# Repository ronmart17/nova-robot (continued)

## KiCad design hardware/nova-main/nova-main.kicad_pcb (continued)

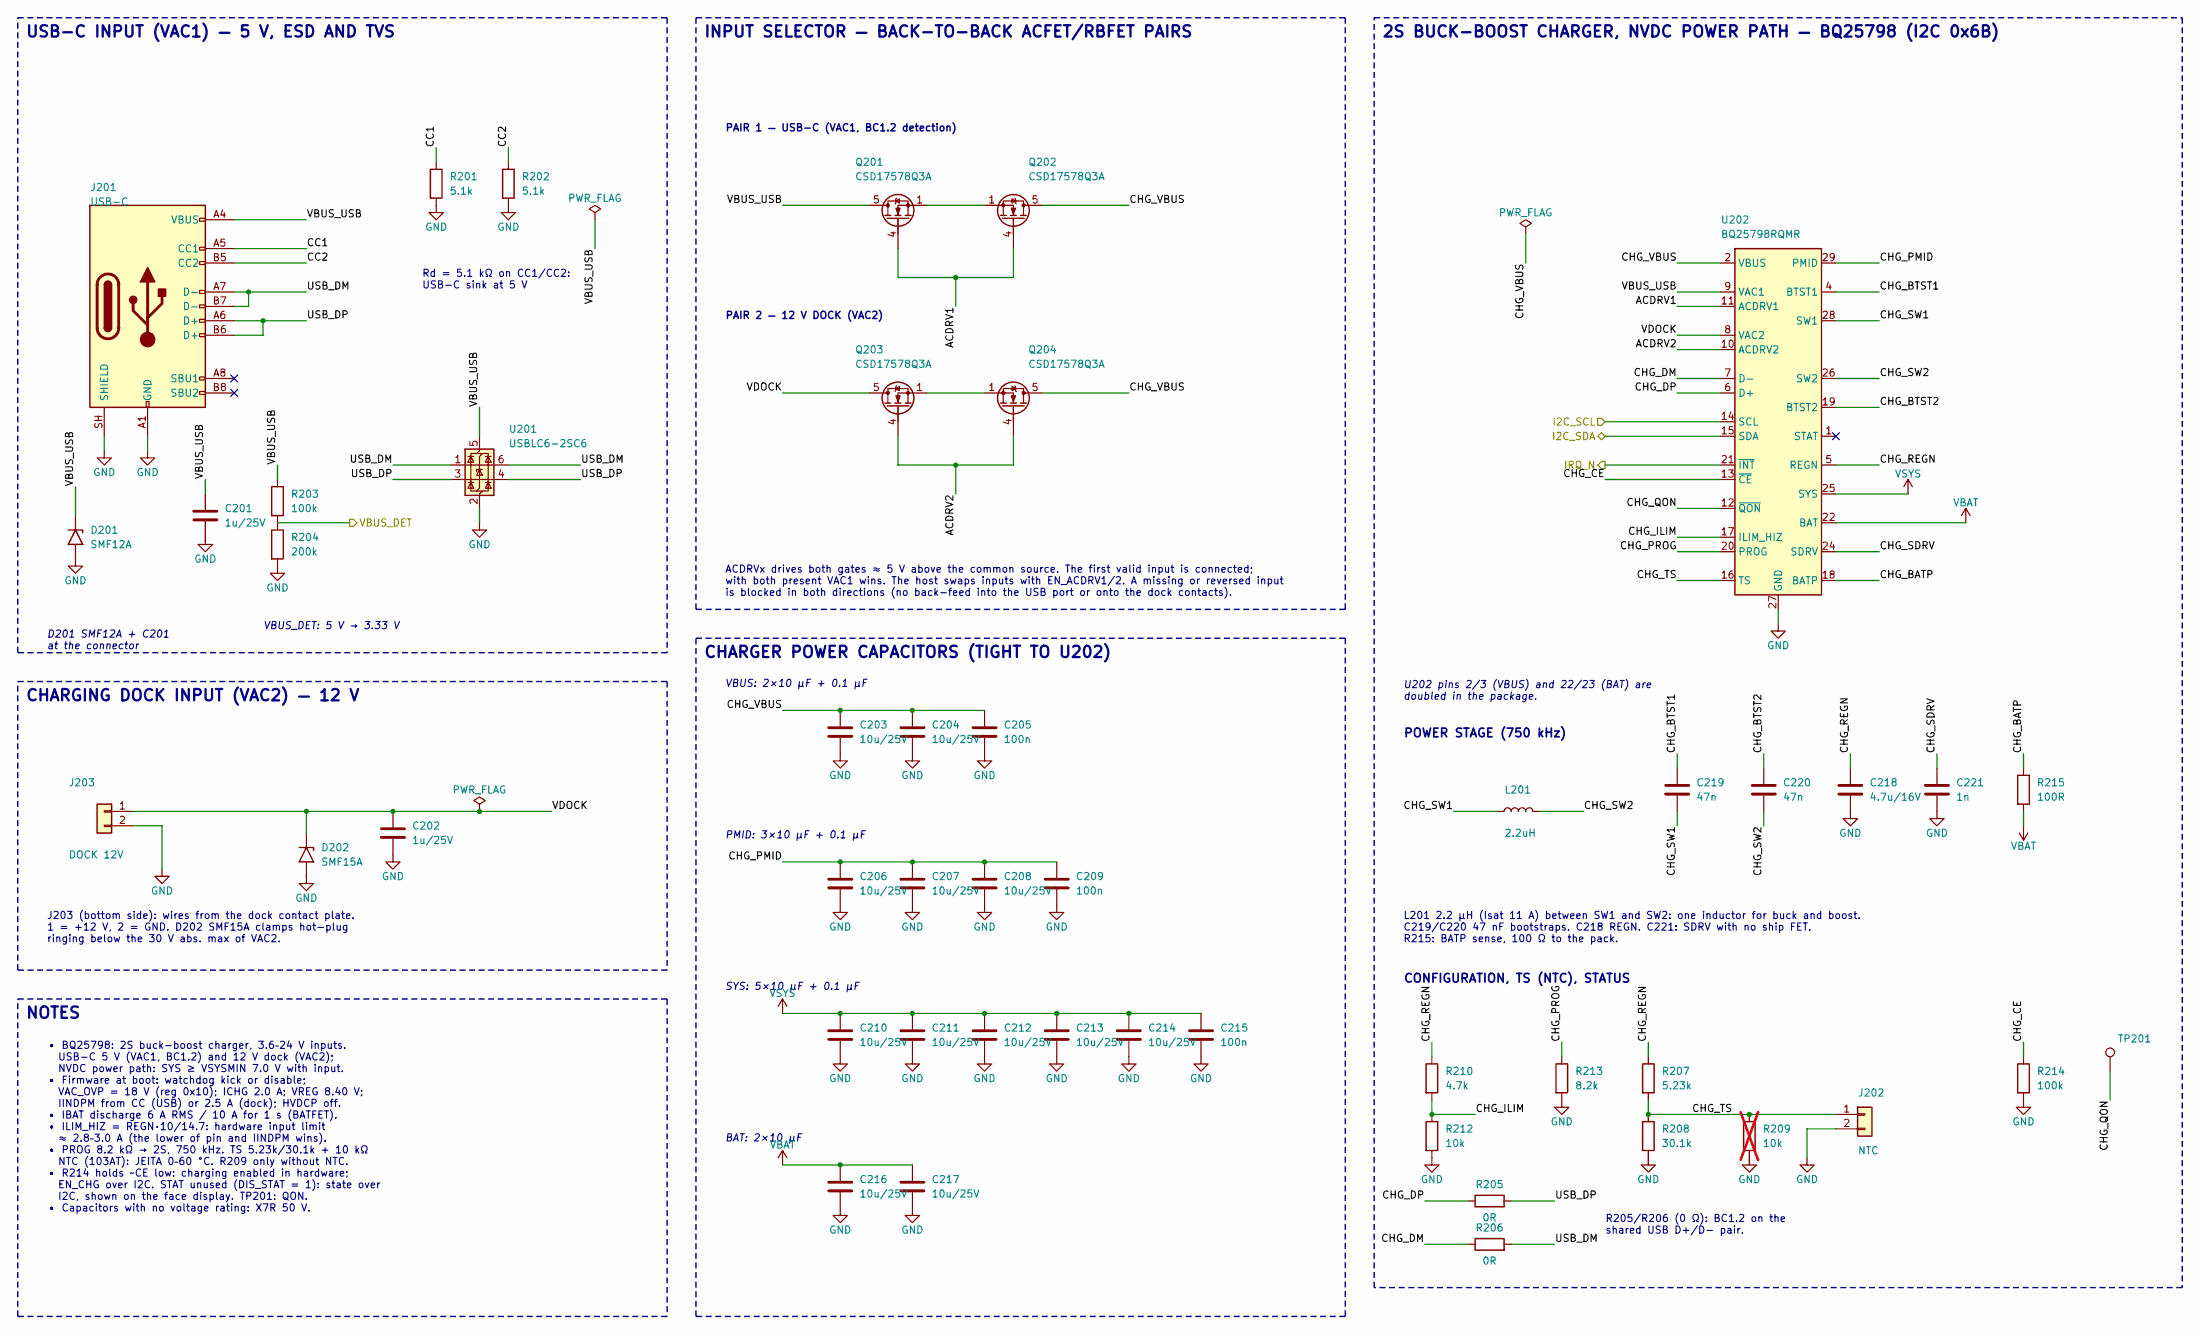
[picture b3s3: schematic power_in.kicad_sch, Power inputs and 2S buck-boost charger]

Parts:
C201, C202: 1u/25V; C_0603_1608Metric; Voltage 25V; MPN CC0603KRX5R8BB105; LCSC C14664
C203, C204, C206, C207, C208, C210, C211, C212, C213, C214, C216, C217: 10u/25V; C_0805_2012Metric; Voltage 25V; MPN CL21A106KAYNNNE; LCSC C15850
C205, C209, C215: 100n; C_0402_1005Metric; Voltage 50V; MPN CL05B104KB54PNC; LCSC C307331
C218: 4.7u/16V; C_0603_1608Metric; Voltage 16V; MPN CL10A475KO8NNNC; LCSC C19666
C219, C220: 47n; C_0402_1005Metric; Voltage 25V; MPN CL05B473KA5NNNC; LCSC C318631
C221: 1n; C_0402_1005Metric; Voltage 50V; MPN CL05B102KB5NNNC; LCSC C14442
D201: SMF12A; D_SMF; MPN SMF12A; LCSC C123800
D202: SMF15A; D_SMF; MPN SMF15A; LCSC C123802
J201: USB-C; USB_C_Receptacle_HRO_TYPE-C-31-M-12_GCT_USB4105; MPN TYPE-C-31-M-12; LCSC C165948
J202: NTC; JST_PH_B2B-PH-K_1x02_P2.00mm_Vertical; MPN B2B-PH-K-S(LF)(SN); LCSC C131337
J203: DOCK 12V; JST_XH_B2B-XH-A_1x02_P2.50mm_Vertical; MPN B2B-XH-A(LF)(SN); LCSC C158012
L201: 2.2uH; L_Sunlord_MWSA0605S; MPN MWSA0605S-2R2MT; LCSC C408463
Q201, Q202, Q203, Q204: CSD17578Q3A; VSON-8_3.3x3.3mm_P0.65mm_NexFET; MPN CSD17578Q3A; LCSC C205986
R201, R202: 5.1k; R_0402_1005Metric; Tolerance 1%; MPN RC0402FR-075K1L; LCSC C105872
R203, R214: 100k; R_0402_1005Metric; Tolerance 1%; MPN RC0402FR-07100KL; LCSC C60491
R204: 200k; R_0402_1005Metric; Tolerance 1%; MPN RC0402FR-07200KL; LCSC C114763
R205, R206: 0R; R_0402_1005Metric; Tolerance 1%; MPN RC0402JR-070RL; LCSC C60485
R207: 5.23k; R_0402_1005Metric; Tolerance 1%; MPN CRCW04025K23FKED; LCSC C2076550
R208: 30.1k; R_0402_1005Metric; Tolerance 1%; MPN ERJ-2RKF3012X; LCSC C2076806
R209: 10k; R_0402_1005Metric; Tolerance 1%; MPN RC0402FR-0710KL; LCSC C60490; not fitted
R210: 4.7k; R_0402_1005Metric; Tolerance 1%; MPN RC0402FR-074K7L; LCSC C105871
R212: 10k; R_0402_1005Metric; Tolerance 1%; MPN RC0402FR-0710KL; LCSC C60490
R213: 8.2k; R_0402_1005Metric; Tolerance 1%; MPN 0402WGF8201TCE; LCSC C25924
R215: 100R; R_0402_1005Metric; Tolerance 1%; MPN RC0402FR-07100RL; LCSC C106232
TP201: TP; TestPoint_Pad_D1.5mm
U201: USBLC6-2SC6; SOT-23-6; MPN USBLC6-2SC6; LCSC C7519
U202: BQ25798RQMR; Texas_RQM0029A_VQFN-29_4x4mm_P0.4mm; MPN BQ25798RQMR; LCSC C2876593

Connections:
/I2C_SCL: U202.14 (SCL); also elsewhere on the board
/I2C_SDA: U202.15 (SDA); also elsewhere on the board
/IRQ_N: U202.21 (~INT); also elsewhere on the board
/USB-C + 12 V dock, BQ25798 charger/ACDRV1: Q201.4 (G), Q202.4 (G), U202.11 (ACDRV1)
/USB-C + 12 V dock, BQ25798 charger/ACDRV2: Q203.4 (G), Q204.4 (G), U202.10 (ACDRV2)
/USB-C + 12 V dock, BQ25798 charger/CC1: J201.A5 (CC1), R201.1
/USB-C + 12 V dock, BQ25798 charger/CC2: J201.B5 (CC2), R202.1
/USB-C + 12 V dock, BQ25798 charger/CHG_BATP: R215.1, U202.18 (BATP)
/USB-C + 12 V dock, BQ25798 charger/CHG_BTST1: C219.1, U202.4 (BTST1)
/USB-C + 12 V dock, BQ25798 charger/CHG_BTST2: C220.1, U202.19 (BTST2)
/USB-C + 12 V dock, BQ25798 charger/CHG_CE: R214.1, U202.13 (~CE)
/USB-C + 12 V dock, BQ25798 charger/CHG_DM: R206.1, U202.7 (D-)
/USB-C + 12 V dock, BQ25798 charger/CHG_DP: R205.1, U202.6 (D+)
/USB-C + 12 V dock, BQ25798 charger/CHG_ILIM: R210.2, R212.1, U202.17 (ILIM_HIZ)
/USB-C + 12 V dock, BQ25798 charger/CHG_PMID: C206.1, C207.1, C208.1, C209.1, U202.29 (PMID)
/USB-C + 12 V dock, BQ25798 charger/CHG_PROG: R213.1, U202.20 (PROG)
/USB-C + 12 V dock, BQ25798 charger/CHG_QON: TP201.1 (1_1), U202.12 (~QON)
/USB-C + 12 V dock, BQ25798 charger/CHG_REGN: C218.1, R207.1, R210.1, U202.5 (REGN)
/USB-C + 12 V dock, BQ25798 charger/CHG_SDRV: C221.1, U202.24 (SDRV)
/USB-C + 12 V dock, BQ25798 charger/CHG_SW1: C219.2, L201.1, U202.28 (SW1)
/USB-C + 12 V dock, BQ25798 charger/CHG_SW2: C220.2, L201.2, U202.26 (SW2)
/USB-C + 12 V dock, BQ25798 charger/CHG_TS: J202.1, R207.2, R208.1, R209.1, U202.16 (TS)
/USB-C + 12 V dock, BQ25798 charger/USB_DM: J201.A7 (D-), J201.B7 (D-), R206.2, U201.1 (I/O1), U201.6 (I/O1)
/USB-C + 12 V dock, BQ25798 charger/USB_DP: J201.A6 (D+), J201.B6 (D+), R205.2, U201.3 (I/O2), U201.4 (I/O2)
/VBUS_DET: R203.2, R204.1; also elsewhere on the board
unnamed: Q201.1 (S), Q201.2 (S), Q201.3 (S), Q202.1 (S), Q202.2 (S), Q202.3 (S)
unnamed: Q203.1 (S), Q203.2 (S), Q203.3 (S), Q204.1 (S), Q204.2 (S), Q204.3 (S)
VBAT: C216.1, C217.1, R215.2, U202.22 (BAT), U202.23 (BAT); also elsewhere on the board
VSYS: C210.1, C211.1, C212.1, C213.1, C214.1, C215.1, U202.25 (SYS); also elsewhere on the board

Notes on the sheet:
USB-C INPUT (VAC1) — 5 V, ESD AND TVS
CHARGING DOCK INPUT (VAC2) — 12 V
NOTES
INPUT SELECTOR — BACK-TO-BACK ACFET/RBFET PAIRS
CHARGER POWER CAPACITORS (TIGHT TO U202)
2S BUCK-BOOST CHARGER, NVDC POWER PATH — BQ25798 (I2C 0x6B)
Rd = 5.1 kΩ on CC1/CC2: USB-C sink at 5 V
VBUS_DET: 5 V → 3.33 V
D201 SMF12A + C201 at the connector
J203 (bottom side): wires from the dock contact plate. 1 = +12 V, 2 = GND. D202 SMF15A clamps hot-plug ringing below the 30 V abs. max of VAC2.
PAIR 1 — USB-C (VAC1, BC1.2 detection)
PAIR 2 — 12 V DOCK (VAC2)
ACDRVx drives both gates ≈ 5 V above the common source. The first valid input is connected; with both present VAC1 wins. The host swaps inputs with EN_ACDRV1/2. A missing or reversed input is blocked in both directions (no back-feed into the USB port or onto the dock contacts).
VBUS: 2×10 µF + 0.1 µF
PMID: 3×10 µF + 0.1 µF
SYS: 5×10 µF + 0.1 µF
BAT: 2×10 µF
U202 pins 2/3 (VBUS) and 22/23 (BAT) are doubled in the package.
POWER STAGE (750 kHz)
L201 2.2 µH (Isat 11 A) between SW1 and SW2: one inductor for buck and boost. C219/C220 47 nF bootstraps. C218 REGN. C221: SDRV with no ship FET. R215: BATP sense, 100 Ω to the pack.
CONFIGURATION, TS (NTC), STATUS
R205/R206 (0 Ω): BC1.2 on the shared USB D+/D− pair.
• BQ25798: 2S buck-boost charger, 3.6–24 V inputs. USB-C 5 V (VAC1, BC1.2) and 12 V dock (VAC2); NVDC power path: SYS ≥ VSYSMIN 7.0 V with input. • Firmware at boot: watchdog kick or disable; VAC_OVP = 18 V (reg 0x10); ICHG 2.0 A; VREG 8.40 V; IINDPM from CC (USB) or 2.5 A (dock); HVDCP off. • IBAT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

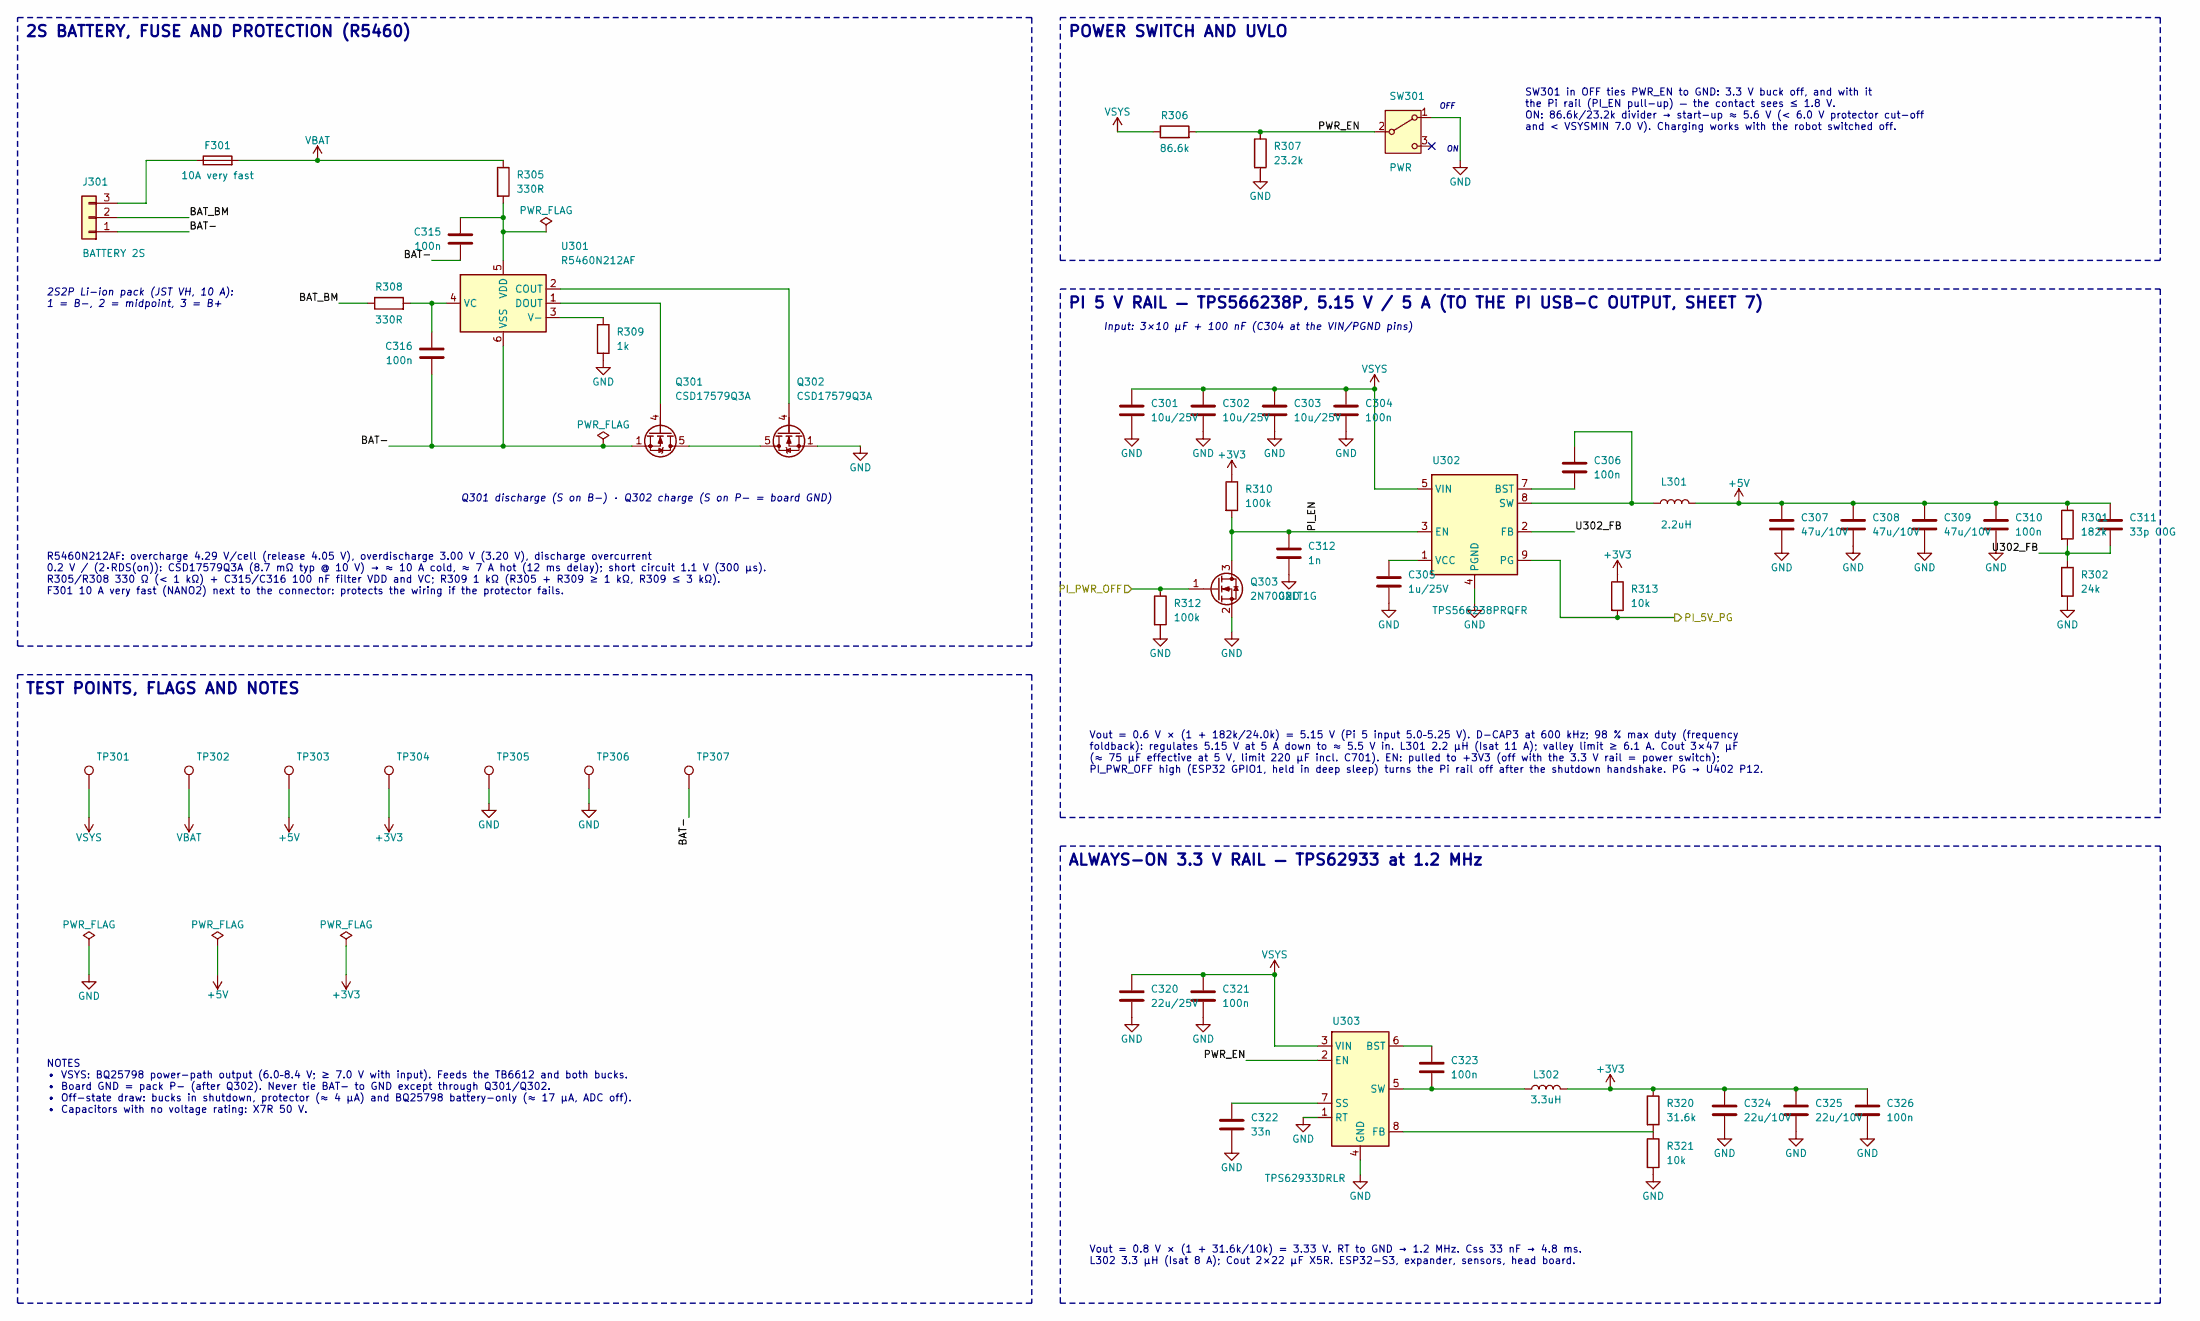
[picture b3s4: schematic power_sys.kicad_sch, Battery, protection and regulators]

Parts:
C301, C302, C303: 10u/25V; C_0805_2012Metric; Voltage 25V; MPN CL21A106KAYNNNE; LCSC C15850
C304, C306, C310, C315, C316, C321, C323, C326: 100n; C_0402_1005Metric; Voltage 50V; MPN CL05B104KB54PNC; LCSC C307331
C305: 1u/25V; C_0402_1005Metric; Voltage 25V; MPN CL05A105KA5NQNC; LCSC C52923
C307, C308, C309: 47u/10V; C_1206_3216Metric; Voltage 10V; MPN CL31A476MPHNNNE; LCSC C96123
C311: 33p C0G; C_0402_1005Metric; Voltage 50V; MPN CL05C330JB5NNNC; LCSC C70465
C312: 1n; C_0402_1005Metric; Voltage 50V; MPN CL05B102KB5NNNC; LCSC C14442
C320: 22u/25V; C_1206_3216Metric; Voltage 25V; MPN CL31A226KAHNNNE; LCSC C12891
C322: 33n; C_0402_1005Metric; Voltage 50V; MPN CL05B333KB5VPNC; LCSC C472437
C324, C325: 22u/10V; C_0805_2012Metric; Voltage 10V; MPN LMK212BJ226MG-T; LCSC C92814
F301: 10A very fast; Fuse_Littelfuse-NANO2-451_453; MPN 0451010.MRL; LCSC C44479
J301: BATTERY 2S; JST_VH_B3P-VH_1x03_P3.96mm_Vertical; MPN B3P-VH(LF)(SN); LCSC C160316
L301: 2.2uH; L_Sunlord_MWSA0605S; MPN MWSA0605S-2R2MT; LCSC C408463
L302: 3.3uH; L_Bourns_SRP5030T; MPN SRP5030T-3R3M; LCSC C189931
Q301, Q302: CSD17579Q3A; VSON-8_3.3x3.3mm_P0.65mm_NexFET; MPN CSD17579Q3A; LCSC C97376
Q303: 2N7002LT1G; SOT-23; MPN 2N7002LT1G; LCSC C16338
R301: 182k; R_0402_1005Metric; Tolerance 1%; MPN RC0402FR-07182KL; LCSC C327365
R302: 24k; R_0402_1005Metric; Tolerance 1%; MPN RC0402FR-0724KL; LCSC C138026
R305, R308: 330R; R_0402_1005Metric; Tolerance 1%; MPN RC0402FR-07330RL; LCSC C105875
R306: 86.6k; R_0402_1005Metric; Tolerance 1%; MPN RC0402FR-0786K6L; LCSC C477807
R307: 23.2k; R_0402_1005Metric; Tolerance 1%; MPN CRCW040223K2FKED; LCSC C2076557
R309: 1k; R_0402_1005Metric; Tolerance 1%; MPN RC0402FR-071KL; LCSC C106235
R310, R312: 100k; R_0402_1005Metric; Tolerance 1%; MPN RC0402FR-07100KL; LCSC C60491
R313, R321: 10k; R_0402_1005Metric; Tolerance 1%; MPN RC0402FR-0710KL; LCSC C60490
R320: 31.6k; R_0402_1005Metric; Tolerance 1%; MPN CRCW040231K6FKED; LCSC C482148
SW301: PWR; SW_SPDT_PCM12; MPN PCM12SMTR; LCSC C221841
TP301, TP302, TP303, TP304, TP305, TP306, TP307: TP; TestPoint_Pad_D1.5mm
U301: R5460N212AF; SOT-23-6; MPN R5460N212AF-TR-FE; LCSC C259717
U302: TPS566238PRQFR; Texas_RQF0009A_VQFN-HR-9_1.5x2mm_P0.5mm; MPN TPS566238PRQFR; LCSC C2876603
U303: TPS62933DRLR; SOT-583-8; MPN TPS62933DRLR; LCSC C3200405

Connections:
/2S battery, protection, 3V3 and Pi 5 V bucks/BAT_BM: J301.2, R308.1
/2S battery, protection, 3V3 and Pi 5 V bucks/PI_EN: C312.1, Q303.3 (D), R310.2, U302.3 (EN)
/2S battery, protection, 3V3 and Pi 5 V bucks/PWR_EN: R306.2, R307.1, SW301.2 (B), U303.2 (EN)
/2S battery, protection, 3V3 and Pi 5 V bucks/U302_FB: C311.2, R301.2, R302.1, U302.2 (FB)
/PI_5V_PG: R313.2, U302.9 (PG); also elsewhere on the board
/PI_PWR_OFF: Q303.1 (G), R312.1; also elsewhere on the board
unnamed: F301.1, J301.3
unnamed: Q301.5 (D), Q302.5 (D)
unnamed: Q301.4 (G), U301.1 (DOUT)
unnamed: Q302.4 (G), U301.2 (COUT)
unnamed: R309.1, U301.3 (V-)
unnamed: C316.1, R308.2, U301.4 (VC)
unnamed: C306.2, U302.7 (BST)
unnamed: C306.1, L301.1, U302.8 (SW)
unnamed: C305.1, U302.1 (VCC)
unnamed: C323.1, U303.6 (BST)
unnamed: R320.2, R321.1, U303.8 (FB)
unnamed: C322.1, U303.7 (SS)
unnamed: C323.2, L302.1, U303.5 (SW)
VBAT: F301.2, R305.1, TP302.1 (1_1); also elsewhere on the board
VSYS: C301.1, C302.1, C303.1, C304.1, C320.1, C321.1, R306.1, TP301.1 (1_1), U302.5 (VIN), U302.6 (VIN), U303.3 (VIN); also elsewhere on the board

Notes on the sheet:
2S BATTERY, FUSE AND PROTECTION (R5460)
POWER SWITCH AND UVLO
PI 5 V RAIL — TPS566238P, 5.15 V / 5 A (TO THE PI USB-C OUTPUT, SHEET 7)
ALWAYS-ON 3.3 V RAIL — TPS62933 at 1.2 MHz
TEST POINTS, FLAGS AND NOTES
2S2P Li-ion pack (JST VH, 10 A): 1 = B−, 2 = midpoint, 3 = B+
Q301 discharge (S on B−) · Q302 charge (S on P− = board GND)
R5460N212AF: overcharge 4.29 V/cell (release 4.05 V), overdischarge 3.00 V (3.20 V), discharge overcurrent 0.2 V / (2·RDS(on)): CSD17579Q3A (8.7 mΩ typ @ 10 V) → ≈ 10 A cold, ≈ 7 A hot (12 ms delay); short circuit 1.1 V (300 µs). R305/R308 330 Ω (< 1 kΩ) + C315/C316 100 nF filter VDD and VC; R309 1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
OFF
SW301 in OFF ties PWR_EN to GND: 3.3 V buck off, and with it the Pi rail (PI_EN pull-up) — the contact sees ≤ 1.8 V. ON: 86.6k/23.2k divider → start-up ≈ 5.6 V (< 6.0 V protector cut-off and < VSYSMIN 7.0 V). Charging works with the robot switched off.
Input: 3×10 µF + 100 nF (C304 at the VIN/PGND pins)
Vout = 0.6 V × (1 + 182k/24.0k) = 5.15 V (Pi 5 input 5.0–5.25 V). D-CAP3 at 600 kHz; 98 % max duty (frequency foldback): regulates 5.15 V at 5 A down to ≈ 5.5 V in. L301 2.2 µH (Isat 11 A); valley limit ≥ 6.1 A. Cout 3×47 µF (≈ 75 µF effective at 5 V, limit 220 µF incl. C701). EN: pulled to +3V3 (o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
Vout = 0.8 V × (1 + 31.6k/10k) = 3.33 V. RT to GND → 1.2 MHz. Css 33 nF → 4.8 ms. L302 3.3 µH (Isat 8 A); Cout 2×22 µF X5R. ESP32-S3, expander, sensors, head board.
NOTES • VSYS: BQ25798 power-path output (6.0–8.4 V; ≥ 7.0 V with input). Feeds the TB6612 and both bucks. • Board GND = pack P− (after Q302). Never tie BAT− to GND except through Q301/Q302. • Off-state draw: bucks in shutdown, protector (≈ 4 µA) and BQ25798 battery-only (≈ 17 µA, ADC off). • Capaci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

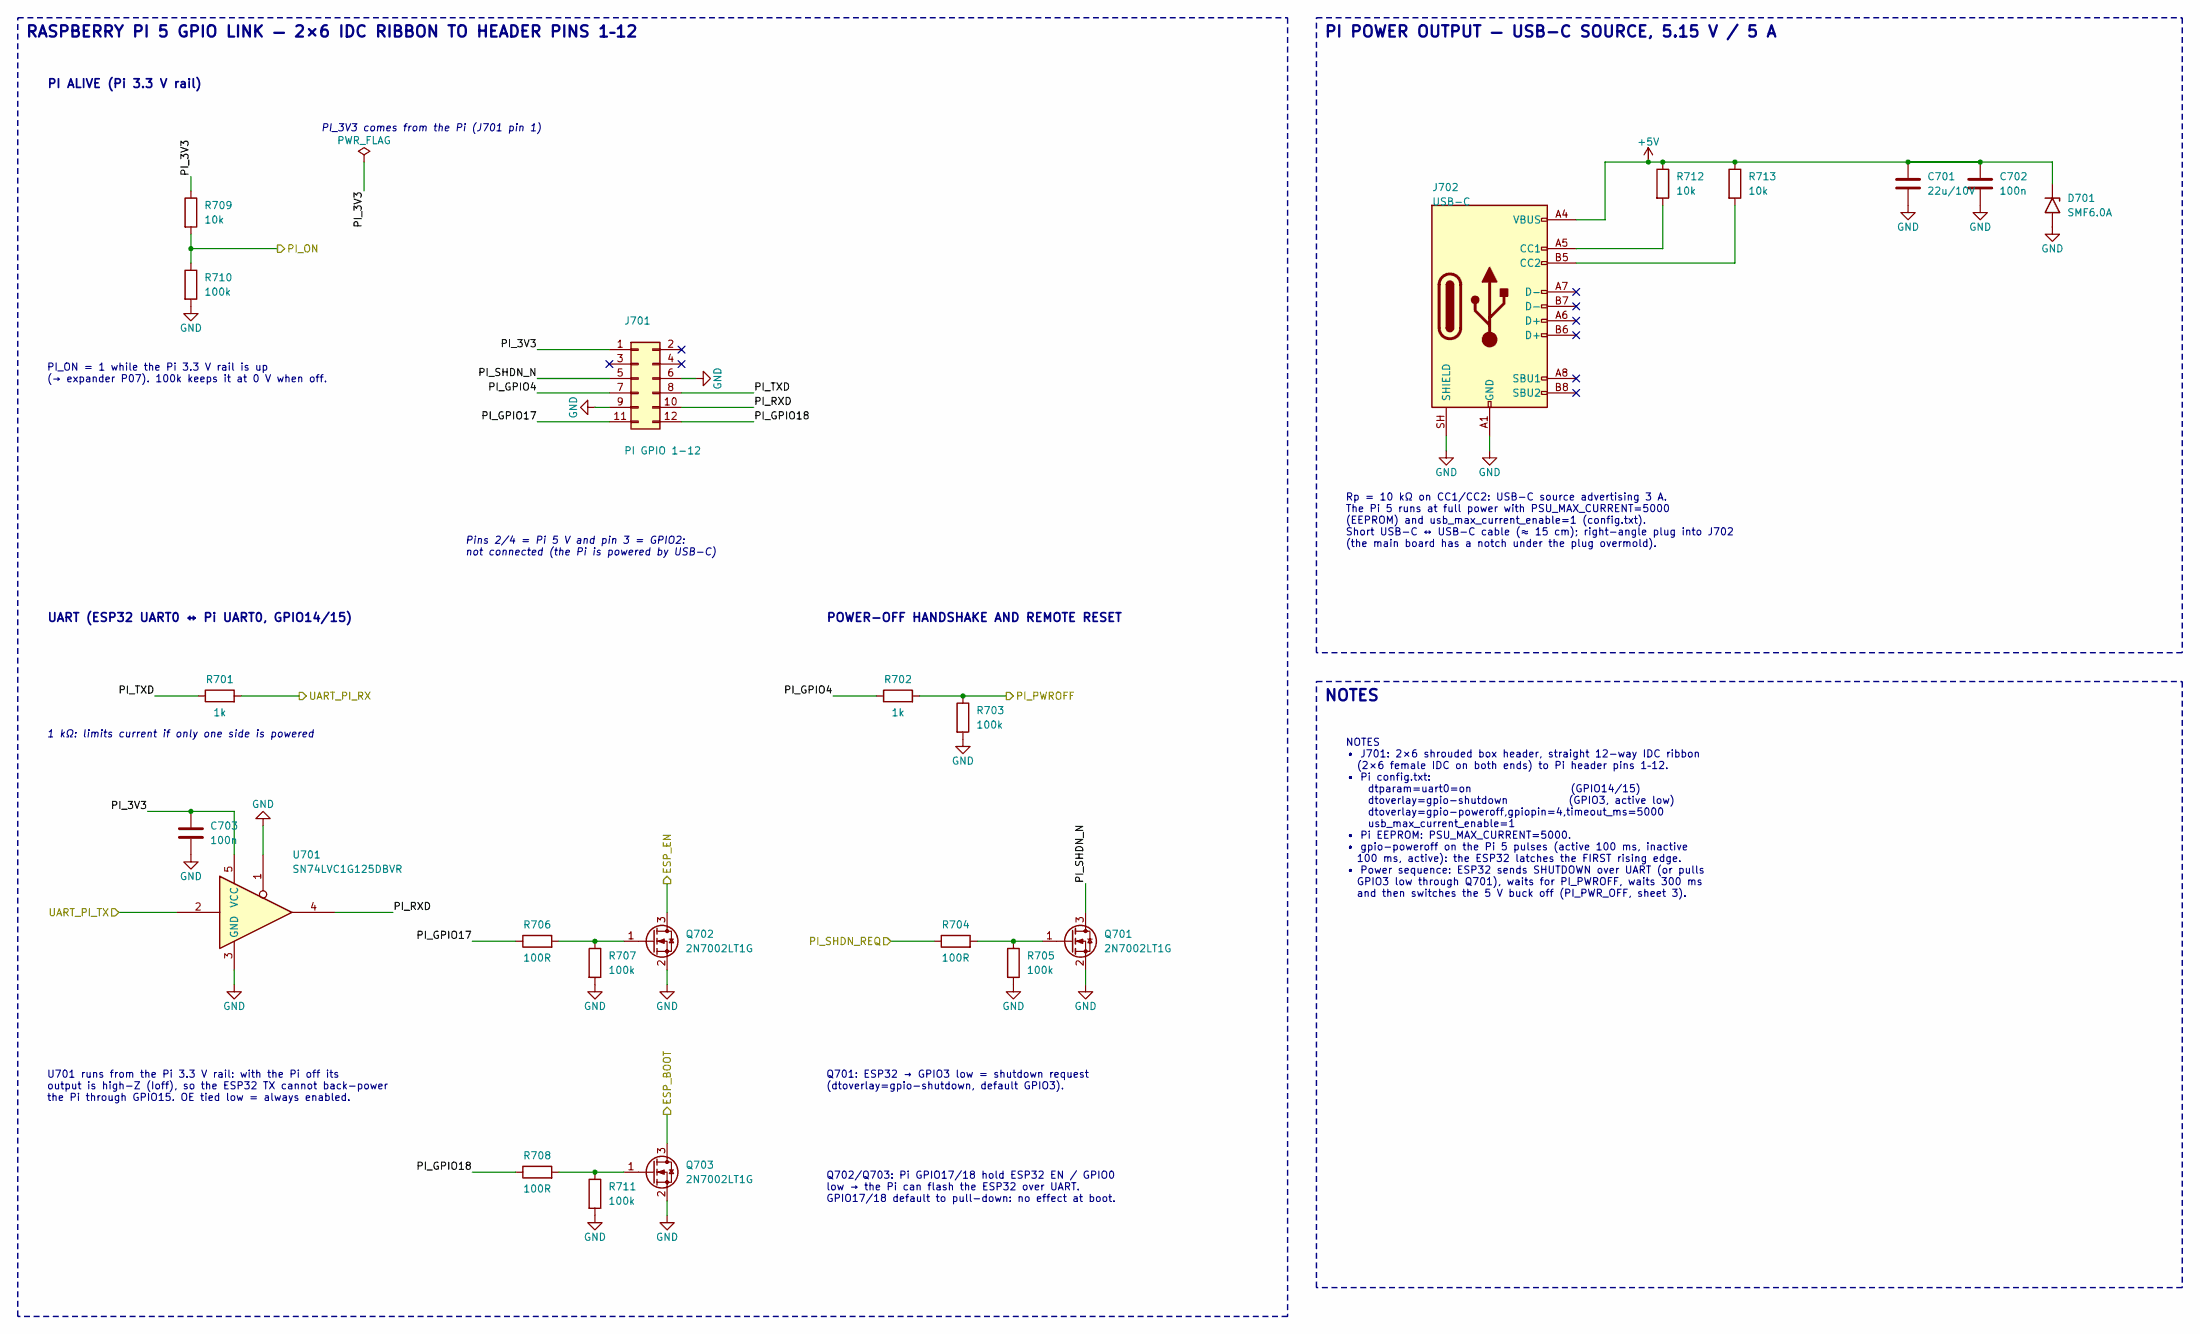
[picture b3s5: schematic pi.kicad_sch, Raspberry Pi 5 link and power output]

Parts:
C701: 22u/10V; C_0805_2012Metric; Voltage 10V; MPN LMK212BJ226MG-T; LCSC C92814
C702, C703: 100n; C_0402_1005Metric; Voltage 50V; MPN CL05B104KB54PNC; LCSC C307331
D701: SMF6.0A; D_SMF; MPN SMF6.0A; LCSC C123790
J701: PI GPIO 1-12; IDC-Header_2x06_P2.54mm_Vertical; MPN 2.54-2*6P box header; LCSC C9136
J702: USB-C; USB_C_Receptacle_HRO_TYPE-C-31-M-12_GCT_USB4105; MPN TYPE-C-31-M-12; LCSC C165948
Q701, Q702, Q703: 2N7002LT1G; SOT-23; MPN 2N7002LT1G; LCSC C16338
R701, R702: 1k; R_0402_1005Metric; Tolerance 1%; MPN RC0402FR-071KL; LCSC C106235
R703, R705, R707, R710, R711: 100k; R_0402_1005Metric; Tolerance 1%; MPN RC0402FR-07100KL; LCSC C60491
R704, R706, R708: 100R; R_0402_1005Metric; Tolerance 1%; MPN RC0402FR-07100RL; LCSC C106232
R709, R712, R713: 10k; R_0402_1005Metric; Tolerance 1%; MPN RC0402FR-0710KL; LCSC C60490
U701: SN74LVC1G125DBVR; SOT-23-5; MPN SN74LVC1G125DBVR; LCSC C23654

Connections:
/ESP_BOOT: Q703.3 (D); also elsewhere on the board
/ESP_EN: Q702.3 (D); also elsewhere on the board
/PI_ON: R709.2, R710.1; also elsewhere on the board
/PI_PWROFF: R702.2, R703.1; also elsewhere on the board
/PI_SHDN_REQ: R704.1; also elsewhere on the board
/Raspberry Pi 5 link and USB-C power/PI_3V3: C703.1, J701.1, R709.1, U701.5 (VCC)
/Raspberry Pi 5 link and USB-C power/PI_GPIO4: J701.7, R702.1
/Raspberry Pi 5 link and USB-C power/PI_GPIO17: J701.11, R706.1
/Raspberry Pi 5 link and USB-C power/PI_GPIO18: J701.12, R708.1
/Raspberry Pi 5 link and USB-C power/PI_RXD: J701.10, U701.4
/Raspberry Pi 5 link and USB-C power/PI_SHDN_N: J701.5, Q701.3 (D)
/Raspberry Pi 5 link and USB-C power/PI_TXD: J701.8, R701.1
/UART_PI_RX: R701.2; also elsewhere on the board
/UART_PI_TX: U701.2; also elsewhere on the board
unnamed: J702.A5 (CC1), R712.2
unnamed: J702.B5 (CC2), R713.2
unnamed: Q701.1 (G), R704.2, R705.1
unnamed: Q702.1 (G), R706.2, R707.1
unnamed: Q703.1 (G), R708.2, R711.1

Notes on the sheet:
RASPBERRY PI 5 GPIO LINK — 2×6 IDC RIBBON TO HEADER PINS 1–12
PI POWER OUTPUT — USB-C SOURCE, 5.15 V / 5 A
NOTES
Pins 2/4 = Pi 5 V and pin 3 = GPIO2: not connected (the Pi is powered by USB-C)
PI ALIVE (Pi 3.3 V rail)
PI_ON = 1 while the Pi 3.3 V rail is up (→ expander P07). 100k keeps it at 0 V when off.
PI_3V3 comes from the Pi (J701 pin 1)
UART (ESP32 UART0 ↔ Pi UART0, GPIO14/15)
1 kΩ: limits current if only one side is powered
U701 runs from the Pi 3.3 V rail: with the Pi off its output is high-Z (Ioff), so the ESP32 TX cannot back-power the Pi through GPIO15. OE tied low = always enabled.
POWER-OFF HANDSHAKE AND REMOTE RESET
Q701: ESP32 → GPIO3 low = shutdown request (dtoverlay=gpio-shutdown, default GPIO3).
Q702/Q703: Pi GPIO17/18 hold ESP32 EN / GPIO0 low → the Pi can flash the ESP32 over UART. GPIO17/18 default to pull-down: no effect at boot.
Rp = 10 kΩ on CC1/CC2: USB-C source advertising 3 A. The Pi 5 runs at full power with PSU_MAX_CURRENT=5000 (EEPROM) and usb_max_current_enable=1 (config.txt). Short USB-C ↔ USB-C cable (≈ 15 cm); right-angle plug into J702 (the main board has a notch under the plug overmold).
NOTES • J701: 2×6 shrouded box header, straight 12-way IDC ribbon (2×6 female IDC on both ends) to Pi header pins 1–12. • Pi config.txt: dtparam=uart0=on (GPIO14/15) dtoverlay=gpio-shutdown (GPIO3, active low) dtoverlay=gpio-poweroff,gpiopin=4,timeout_ms=5000 usb_max_current_enable=1 • Pi EEPROM: P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

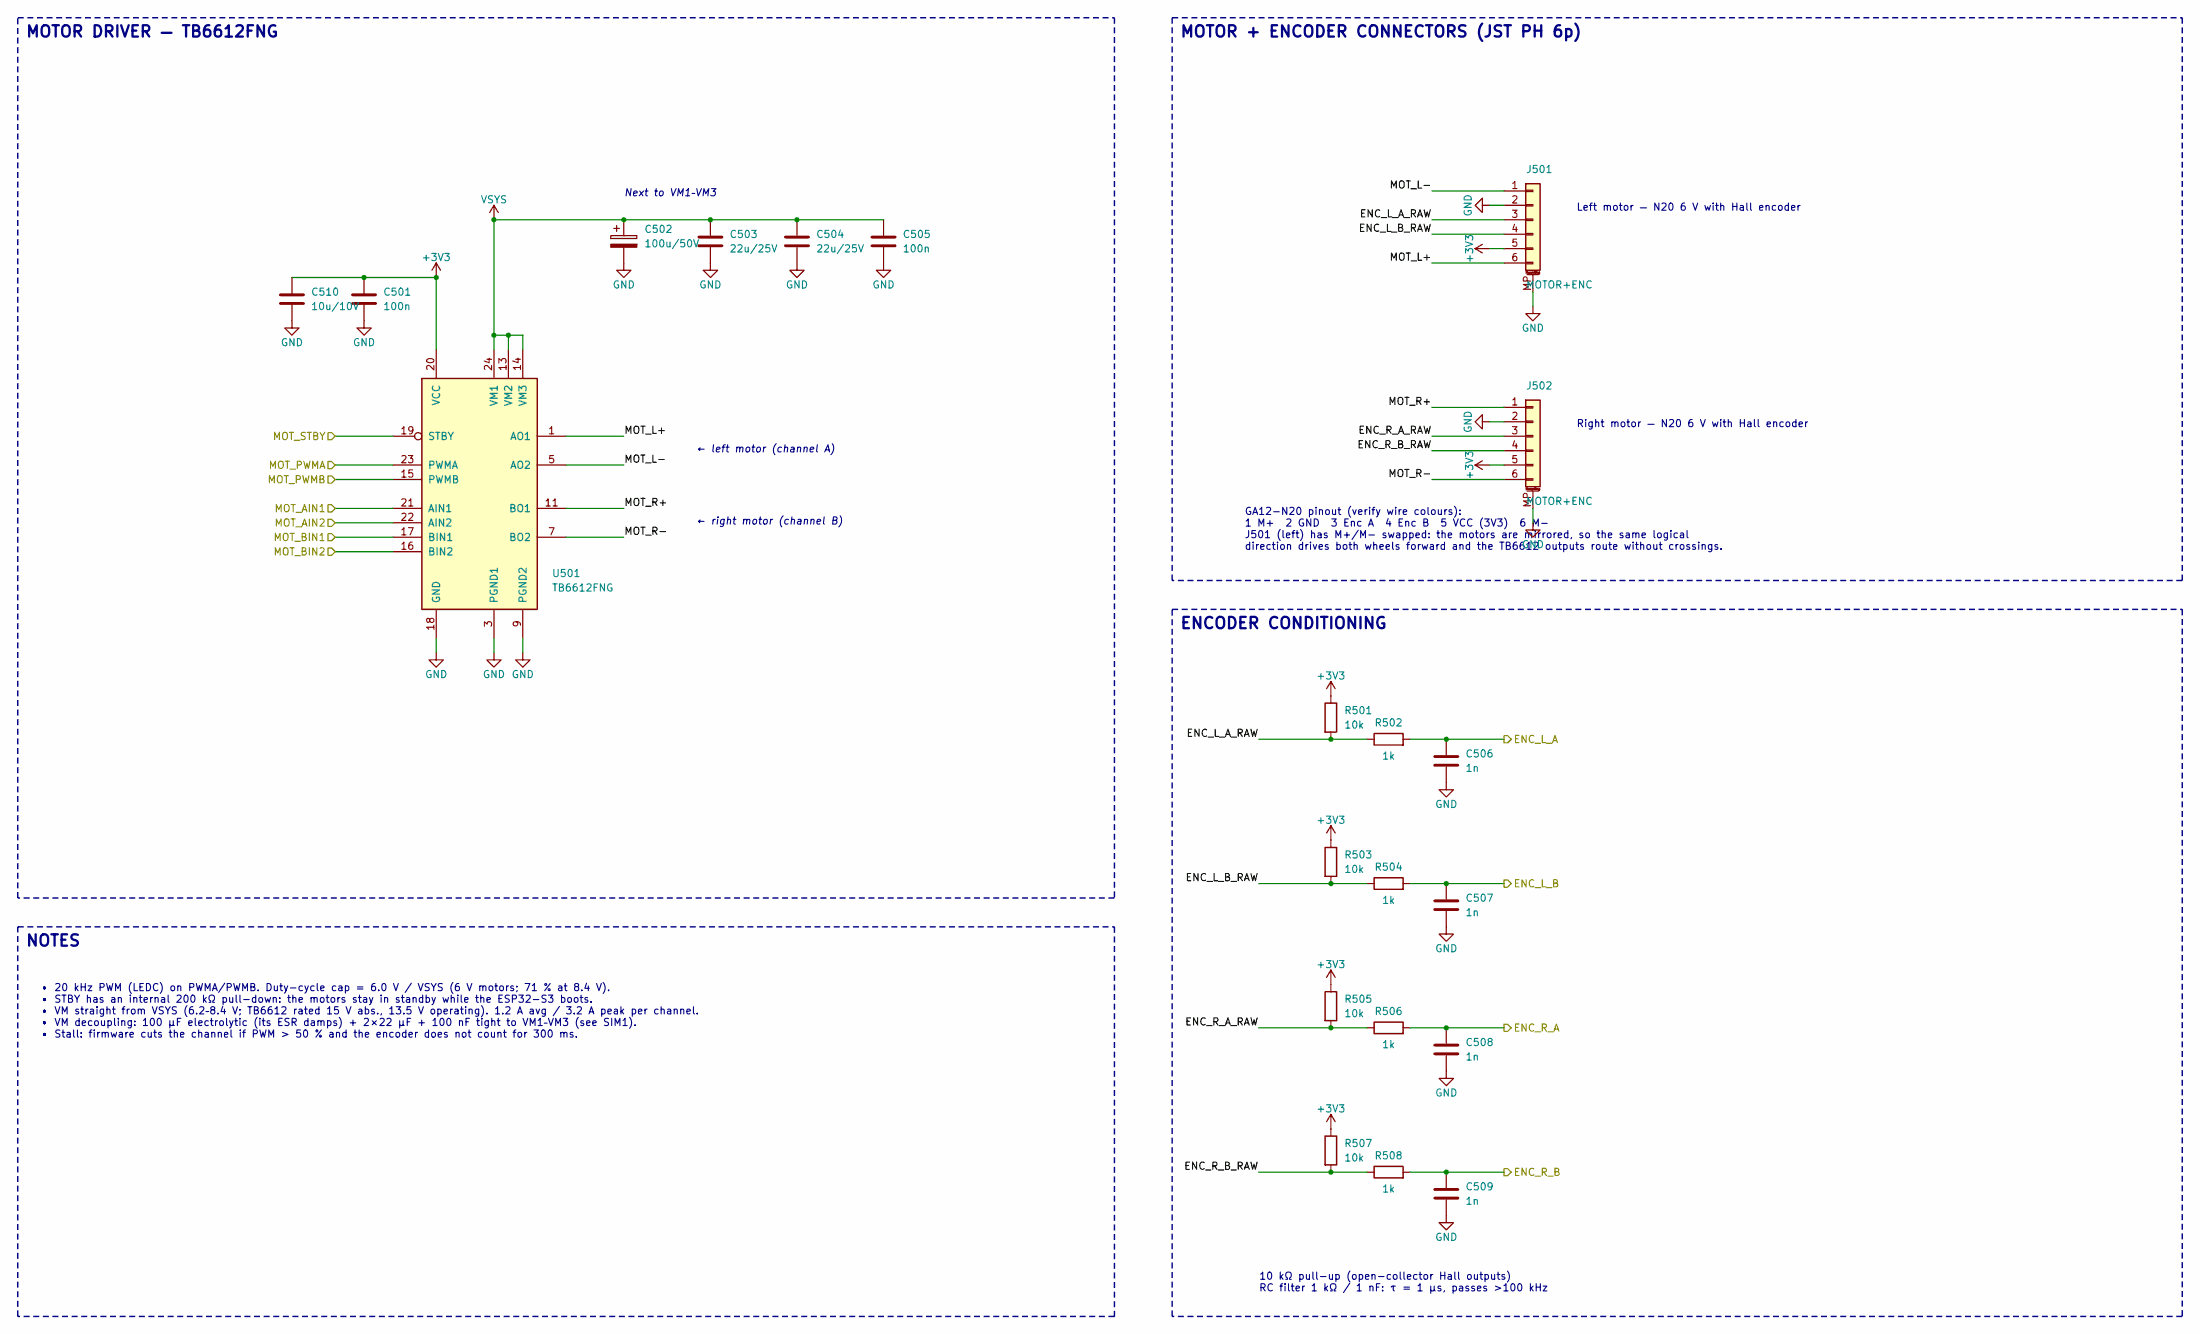
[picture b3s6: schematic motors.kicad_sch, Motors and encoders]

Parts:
C501, C505: 100n; C_0402_1005Metric; Voltage 50V; MPN CL05B104KB54PNC; LCSC C307331
C502: 100u/50V; CP_Elec_6.3x7.7; Voltage 50V; MPN EEE-FTH101XAP; LCSC C165974
C503, C504: 22u/25V; C_1206_3216Metric; Voltage 25V; MPN CL31A226KAHNNNE; LCSC C12891
C506, C507, C508, C509: 1n; C_0402_1005Metric; Voltage 50V; MPN CL05B102KB5NNNC; LCSC C14442
C510: 10u/10V; C_0603_1608Metric; Voltage 10V; MPN CC0603KRX5R6BB106; LCSC C326057
J501, J502: MOTOR+ENC; JST_PH_S6B-PH-SM4-TB_1x06-1MP_P2.00mm_Horizontal; MPN S6B-PH-SM4-TB(LF)(SN); LCSC C265405
R501, R503, R505, R507: 10k; R_0402_1005Metric; Tolerance 1%; MPN RC0402FR-0710KL; LCSC C60490
R502, R504, R506, R508: 1k; R_0402_1005Metric; Tolerance 1%; MPN RC0402FR-071KL; LCSC C106235
U501: TB6612FNG; SSOP-24_5.3x8.2mm_P0.65mm; MPN TB6612FNG,C,8,EL; LCSC C141517

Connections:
/ENC_L_A: C506.1, R502.2; also elsewhere on the board
/ENC_L_B: C507.1, R504.2; also elsewhere on the board
/ENC_R_A: C508.1, R506.2; also elsewhere on the board
/ENC_R_B: C509.1, R508.2; also elsewhere on the board
/MOT_AIN1: U501.21 (AIN1); also elsewhere on the board
/MOT_AIN2: U501.22 (AIN2); also elsewhere on the board
/MOT_BIN1: U501.17 (BIN1); also elsewhere on the board
/MOT_BIN2: U501.16 (BIN2); also elsewhere on the board
/MOT_PWMA: U501.23 (PWMA); also elsewhere on the board
/MOT_PWMB: U501.15 (PWMB); also elsewhere on the board
/MOT_STBY: U501.19 (STBY); also elsewhere on the board
/Motors and encoders/ENC_L_A_RAW: J501.3, R501.2, R502.1
/Motors and encoders/ENC_L_B_RAW: J501.4, R503.2, R504.1
/Motors and encoders/ENC_R_A_RAW: J502.3, R505.2, R506.1
/Motors and encoders/ENC_R_B_RAW: J502.4, R507.2, R508.1
/Motors and encoders/MOT_L+: J501.6, U501.1 (AO1), U501.2 (AO1)
/Motors and encoders/MOT_L-: J501.1, U501.5 (AO2), U501.6 (AO2)
/Motors and encoders/MOT_R+: J502.1, U501.11 (BO1), U501.12 (BO1)
/Motors and encoders/MOT_R-: J502.6, U501.7 (BO2), U501.8 (BO2)
VSYS: C502.1, C503.1, C504.1, C505.1, U501.13 (VM2), U501.14 (VM3), U501.24 (VM1); also elsewhere on the board

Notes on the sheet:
MOTOR DRIVER — TB6612FNG
MOTOR + ENCODER CONNECTORS (JST PH 6p)
ENCODER CONDITIONING
NOTES
Next to VM1–VM3
← left motor (channel A)
← right motor (channel B)
Left motor — N20 6 V with Hall encoder
Right motor — N20 6 V with Hall encoder
GA12-N20 pinout (verify wire colours): 1 M+ 2 GND 3 Enc A 4 Enc B 5 VCC (3V3) 6 M- J501 (left) has M+/M− swapped: the motors are mirrored, so the same logical direction drives both wheels forward and the TB6612 outputs route without crossings.
10 kΩ pull-up (open-collector Hall outputs) RC filter 1 kΩ / 1 nF: τ = 1 µs, passes >100 kHz
• 20 kHz PWM (LEDC) on PWMA/PWMB. Duty-cycle cap = 6.0 V / VSYS (6 V motors; 71 % at 8.4 V). • STBY has an internal 200 kΩ pull-down: the motors stay in standby while the ESP32-S3 boots. • VM straight from VSYS (6.2–8.4 V; TB6612 rated 15 V abs., 13.5 V operating). 1.2 A avg / 3.2 A peak per channe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
